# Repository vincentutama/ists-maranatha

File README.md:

# ists-maranatha
PKM-KC 2019 Integrated Smart Transfer Switch by Dimitri Jeremy et al.

## Progres 80%
- [x] Switching sudah OK
- [x] Pengambilan data (Arus, tegangan) sudah OK
- [ ] Sensing listrik AC belum

Masalah:
* leakage AC current
* ADC fail karna ada Arus AC PLN masuk ke jaringan DC lewat inverter jadi program exit
* Safety (SSR fail close)

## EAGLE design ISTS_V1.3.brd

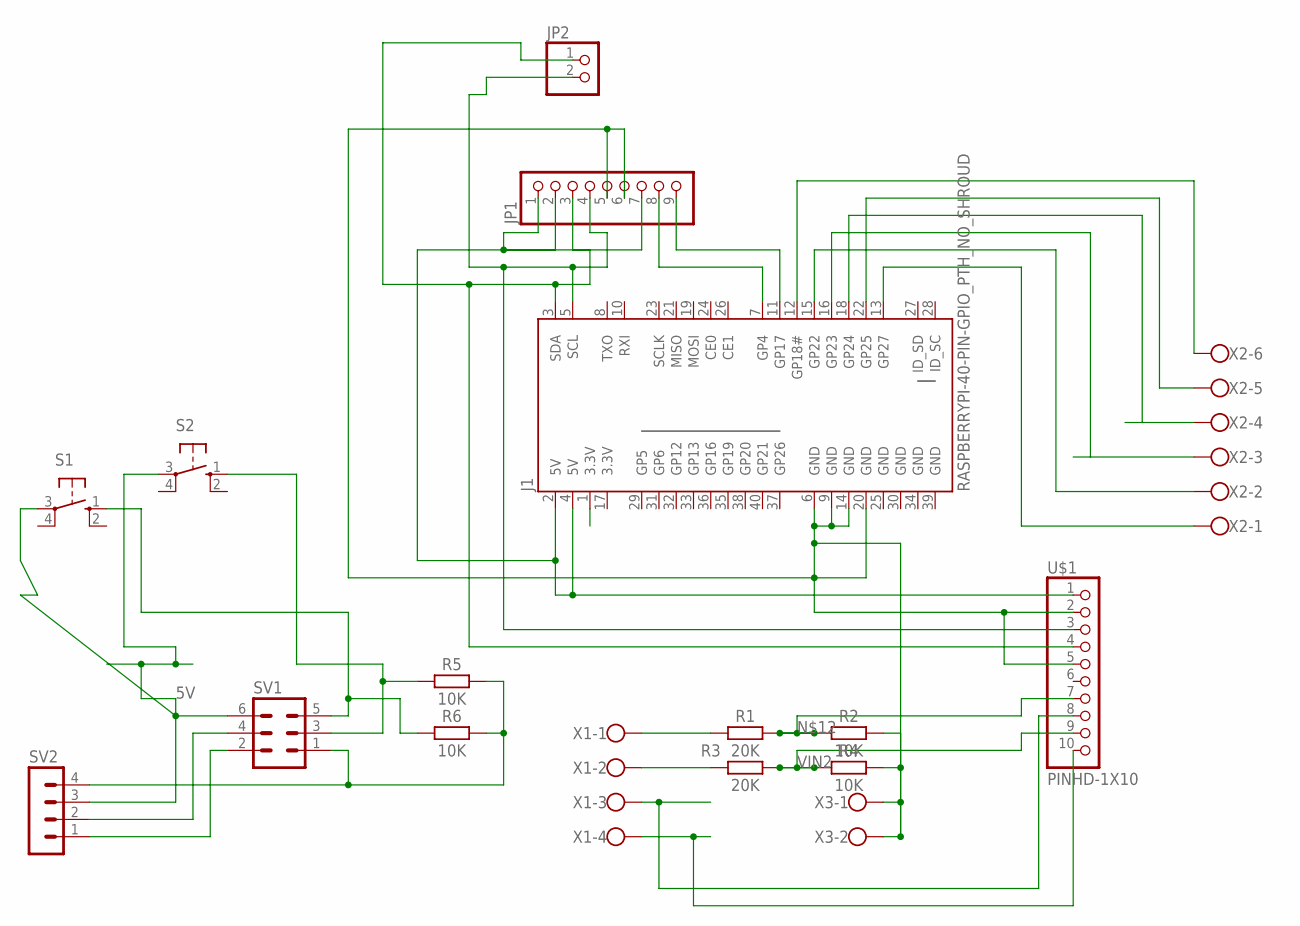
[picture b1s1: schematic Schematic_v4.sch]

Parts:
J1: RASPBERRYPI-40-PIN-GPIO_PTH_NO_SHROUD; 2X20
JP1: PINHD-1X9; 1X09-BIG
JP2: PINHD-1X2; 1X02
R1, R3: 20K; RESC3216X70
R2, R4, R5, R6: 10K; RESC3216X70
S1, S2: 40-XX; B3F-40XX
SV1: MA03-2
SV2: MA04-1
U$1: PINHD-1X10; 1X10-BIG
X1: W237-4
X2: W237-136
X3: W237-102

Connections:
3.3V: J1.17 (3.3V)
5V: S1.3, S2.3, SV1.6, SV2.3
GND: J1.6 (GND), J1.9 (GND), J1.14 (GND), J1.20 (GND), J1.25 (GND), J1.30 (GND), J1.34 (GND), J1.39 (GND), JP1.5, JP1.6, R2.2, R4.2, U$1.2, U$1.5, X3.1, X3.2
unnamed: J1.13 (GP27), X2.1
unnamed: J1.15 (GP22), X2.2
unnamed: R1.1, X1.1
unnamed: J1.2 (5V), J1.4 (5V), JP1.1, JP1.2, JP1.7, U$1.1
unnamed: SV1.4, SV2.2
unnamed: R3.1, X1.2
unnamed: R5.2, R6.2, SV1.1, SV2.4
unnamed: J1.5 (SCL), JP1.4, JP2.2, U$1.3
unnamed: U$1.8, X1.3
unnamed: U$1.10, X1.4
unnamed: J1.16 (GP23), X2.3
unnamed: R1.2, R2.1, U$1.7
unnamed: J1.18 (GP24), X2.4
unnamed: J1.22 (GP25), X2.5
unnamed: J1.12 (GP18#), X2.6
unnamed: J1.11 (GP17), JP1.9
unnamed: J1.7 (GP4), JP1.8
unnamed: SV1.2, SV2.1
unnamed: R6.1, S1.1 (S), SV1.5
unnamed: R5.1, S2.1 (S), SV1.3
unnamed: J1.3 (SDA), JP1.3, JP2.1, U$1.4
VIN2: R3.2, R4.1, U$1.9

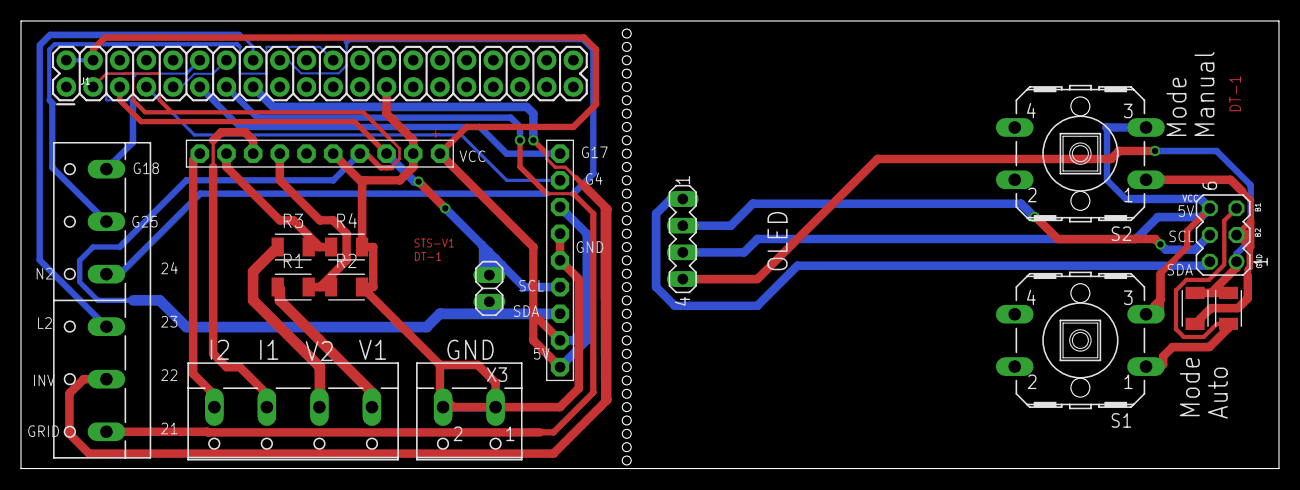
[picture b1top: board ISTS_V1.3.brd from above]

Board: 2 copper layers, 119.7 x 42.6 mm, 17 parts (0 on the bottom side), 24 nets.

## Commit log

2020-08-06 Rename Schematic_v4.brd to ISTS_V1.3.brd
2020-08-06 Rename Schematic_v4.sch to ISTS_V1.3.sch
2020-08-14 Uploaded battery datasheet
    Narada 12NDT200S

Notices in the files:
parts and their libraries:
SparkFun-Connectors: Licensing: Creative Commons ShareAlike 4.0 International - https://creativecommons.org/licenses/by-sa/4.0
